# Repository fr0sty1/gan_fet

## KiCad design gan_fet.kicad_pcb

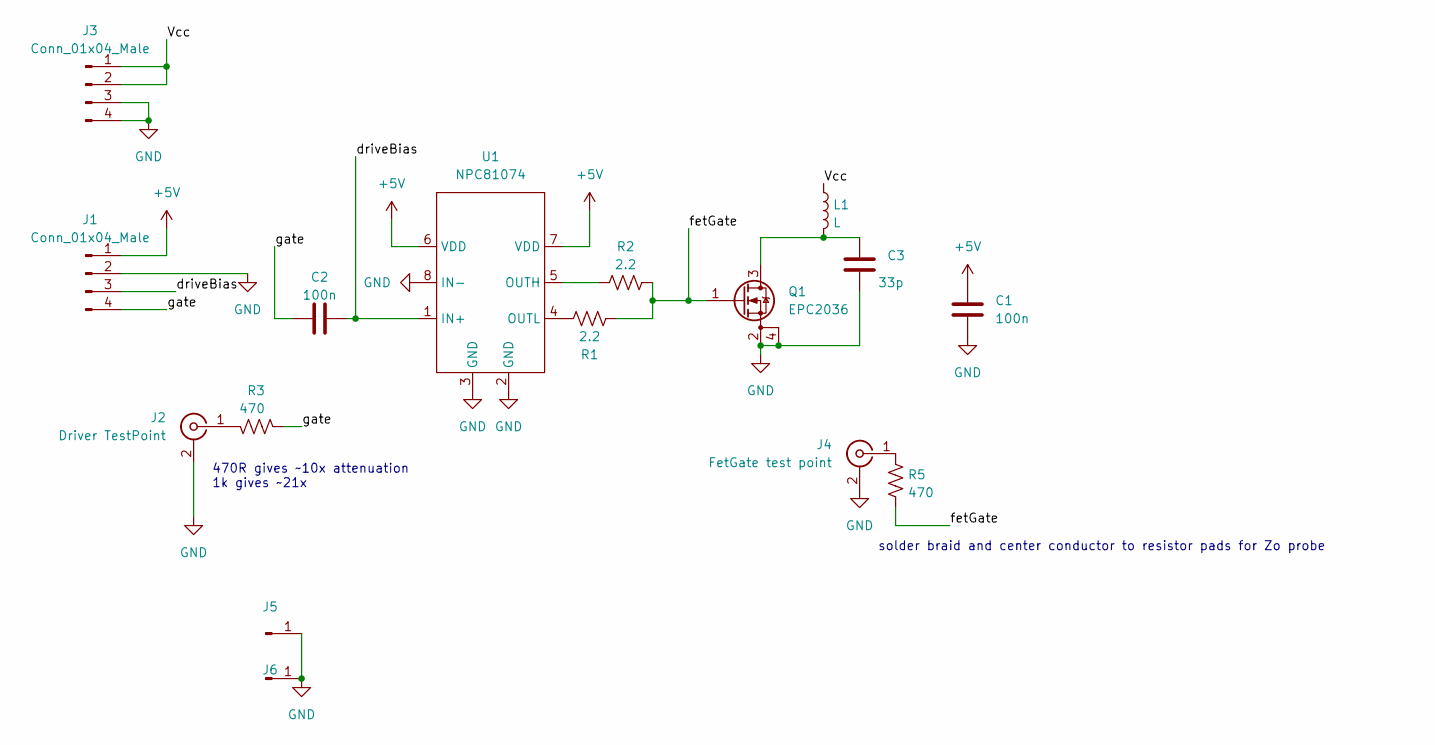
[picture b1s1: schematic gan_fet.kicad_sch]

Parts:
C1, C2: 100n; C_1206_3216Metric
C3: 33p; C_1206_3216Metric
J1, J3: Conn_01x04_Male; PinHeader_1x04_P2.54mm_Vertical
J2: Driver TestPoint; SMA_Samtec_SMA-J-P-X-ST-EM1_EdgeMount
J4: FetGate test point; SMA_Samtec_SMA-J-P-X-ST-EM1_EdgeMount
J5, J6: (no value)
L1: L; R_Axial_DIN0204_L3.6mm_D1.6mm_P5.08mm_Horizontal
Q1: EPC2036; epc2036
R1, R2: 2.2; R_0805_2012Metric_Pad1.20x1.40mm_HandSolder
R3: 470; R_0805_2012Metric
R5: 470; R_0805_2012Metric_Pad1.20x1.40mm_HandSolder
U1: NPC81074; SOIC-8_3.9x4.9mm_P1.27mm

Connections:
+5V: C1.1, J1.1, U1.6 (VDD), U1.7 (VDD)
/Vcc: J3.1, J3.2, L1.1
/driveBias: C2.1, J1.3, U1.1 (IN+)
/fetGate: Q1.1 (G), R1.2, R2.2, R5.2
/gate: C2.2, J1.4, R3.2
GND: C1.2, C3.2, J1.2, J2.2 (Ext), J3.3, J3.4, J4.2 (Ext), J5.1, J6.1, Q1.2 (S), Q1.4 (Source), U1.2 (GND), U1.3 (GND), U1.8 (IN-)
unnamed: C3.1, L1.2, Q1.3 (D)
unnamed: J2.1 (In), R3.1
unnamed: J4.1 (In), R5.1
unnamed: R1.1, U1.4 (OUTL)
unnamed: R2.1, U1.5 (OUTH)

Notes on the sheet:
470R gives ~10x attenuation 1k gives ~21x
solder braid and center conductor to resistor pads for Zo probe

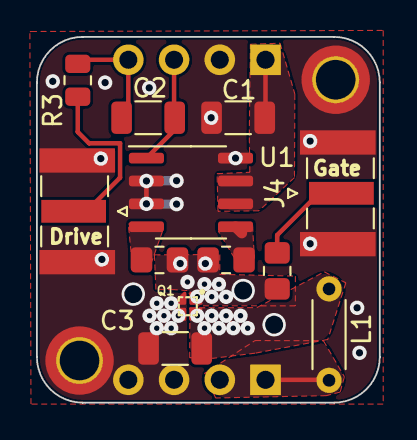
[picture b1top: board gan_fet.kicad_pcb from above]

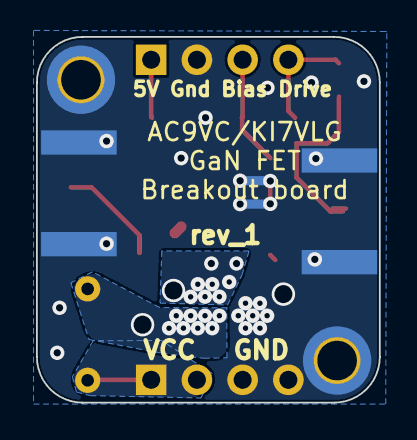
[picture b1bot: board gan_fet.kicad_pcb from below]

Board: 2 copper layers, 19.1 x 20.3 mm, 16 parts (2 on the bottom side), 11 nets.

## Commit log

2022-08-05 some misc fiddling with the footprint and a centered model.
2022-08-10 rev_1 board
2023-01-03 add some labels to schematic
